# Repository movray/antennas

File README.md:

# Antennas

Printed PCB antennas, designed as code and checked by simulation. One directory per antenna type,
each with its simulation scripts, the KiCad project, etching masks and a `STATUS.md`.
Single-sided boards without parts except the coax: home etching (toner transfer) or any PCB maker.

| Antenna | Type | Band | Simulated on 1.6 mm FR4 | Board |
|---|---|---|---|---|
| [dipole-868](dipole-868/) | Half-wave dipole, reference antenna | LoRa / EU868 | 2.0 dBi, SWR < 1.3 | 147 x 22 mm |
| [moxon-868](moxon-868/) | Moxon rectangle, directional | LoRa / EU868 | 5.3 dBi, F/B 13-14 dB, SWR < 1.2 | 117 x 58 mm |

| dipole-868 | moxon-868 |
|---|---|
|  |  |

> **Status: simulated, not yet measured.** The numbers above come from NEC2 and openEMS simulations.
> The boards have not been built and measured yet; real FR4 (er 4.2-4.7) can move the frequency by
> a few percent. Results of RSSI measurements will be added here.

## How these antennas were made

The antennas were designed together with an LLM: **Claude (Anthropic), working in
[Claude Code](https://claude.com/claude-code)** on the author's machine. The author set the goals
(band, gain, directivity, size, home etching, no VNA available for tuning) and made the decisions;
Claude chose the antenna types together with the author, wrote all scripts in this repository, ran the
simulations and interpreted the results. Nothing was taken from an existing antenna design file.

The workflow, per antenna:

1. **Free-space design with NEC2** (`sim.py`, nec2c, the C port of NEC2): wire model,
   optimises the dimensions for match, gain and front/back ratio in the band.
2. **Check and tuning on FR4 with FDTD** (`sim_fdtd.py`, [openEMS](https://openems.de) with its CSXCAD
   Python interface): NEC2 cannot model the substrate, so the printed strips on 1.6 mm FR4 are simulated
   in 3D, including the dielectric losses. For the Moxon a parameter sweep plus a Nelder-Mead
   optimisation ([SciPy](https://scipy.org)) found the board dimensions.
3. **Circuit as code** (`board.py`, [SKiDL](https://github.com/devbisme/skidl)): antenna and coax feed as
   a netlist.
4. **Readable schematic** (`schematic.py`,
   [kicad-schematic-builder](https://github.com/movray/kicad-schematic-builder)): draws the KiCad schematic
   from the netlist and checks that both agree.
5. **PCB with the KiCad 9 pcbnew Python API** (`layout.py`): writes the antenna footprint from the simulated
   dimensions, places it, adds outline and holes, runs the DRC with `kicad-cli` and writes the etching masks.

Because every step is a script, a change in the simulation flows through to the board by re-running
the scripts; nothing was drawn by hand.

### Lessons learned

* Strips on one side of 1.6 mm FR4 get about **14 % shorter** than in free space (`K_FR4 = 0.86`,
  openEMS, dipole resonant at 868.7 MHz), not the ~5 % that is often assumed.
* Antennas with coupled elements (Moxon, Yagi) **do not just scale** with that factor: the substrate also
  changes the coupling between the elements. The NEC design x 0.86 gave only 7 dB front/back on FR4.
  They have to be tuned in a simulator that models the substrate.
* On FR4 the printed Moxon reaches about 14.5 dB front/back at best (in free space > 25 dB). If you need more,
  build it from wire on a plastic frame; then the NEC2 dimensions apply directly.
* openEMS: simulating only one half of a mirror-symmetric antenna with a PEC wall gives the same result
  (checked against the full model) in about 1/10 of the time.

## Tools to re-run

* nec2c (Debian/Ubuntu package `nec2c`)
* openEMS and CSXCAD with their Python modules (built from source,
  [openEMS-Project](https://github.com/thliebig/openEMS-Project)), plus numpy, scipy, h5py
* KiCad 9 (its Python `pcbnew` module, `kicad-cli`)
* SKiDL and kicad-schematic-builder for the schematic

The `Regenerate` section in each antenna's README lists the commands.

## License

* Hardware (KiCad projects, footprints, etching masks, dimensions, documentation):
  [CERN-OHL-P-2.0](LICENSES/CERN-OHL-P-2.0.txt)
* Scripts (`*.py`): [MIT](LICENSES/MIT.txt)

See [LICENSE](LICENSE). Use, modify, build and sell freely; keep the copyright notice.
No warranty: these are simulated designs, check them before you rely on them.

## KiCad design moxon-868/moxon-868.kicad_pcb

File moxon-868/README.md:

# moxon-868

Directional PCB antenna for LoRa 868 MHz: a Moxon rectangle printed on FR4.
On 1.6 mm FR4 (openEMS): about 5.3 dBi and 13-14 dB front/back ratio in the EU868 band, SWR < 1.2
at 50 Ohm without a matching network. Single-sided, no parts except the coax: home etching or JLCPCB.

Compared to a typical cheap SMA stub antenna (real gain often around 0 dBi) that is about 5 dB more in the
beam direction - roughly 1.8 x the range - and signals from behind are ~25 x weaker.

## Files

| File | Purpose |
|---|---|
| `sim.py` | NEC2 model (nec2c), free-space design for 868 MHz, writes `moxon-868-dims.json` |
| `sim_fdtd.py` | openEMS (FDTD) model on FR4: sweep and optimisation of the board dimensions (`board_mm`) |
| `STATUS.md` | How the FR4 dimensions were found, all simulation results |
| `moxon-868-dims.json` | Simulated dimensions: free space and on FR4 (input for `layout.py`) |
| `board.py` | Circuit (SKiDL): antenna AE1 and coax feed J1 |
| `schematic.py` | Draws the schematic with [kicad-schematic-builder](https://github.com/movray/kicad-schematic-builder) and checks it against the netlist |
| `moxon-868.kicad_sch` | Generated schematic |
| `layout.py` | Writes the antenna and feed footprints from the dimensions, builds the PCB, DRC, etching masks |
| `moxon-868.pretty/` | Generated footprints `Moxon_868` and `CoaxFeed_Gap2mm` |
| `moxon-868.kicad_pcb` | Generated PCB (open in KiCad) |
| `moxon-868-etch-mirrored.pdf` | Etching mask for toner transfer (mirrored, 1:1 on A4) |
| `moxon-868-etch-topview.pdf` | Same mask unmirrored, as seen from the copper side (for checking) |

## Regenerate

```bash
/usr/bin/python3 sim.py          # NEC2 optimisation -> moxon-868-dims.json (needs nec2c on the PATH)
~/.venvs/openems/bin/python sim_fdtd.py --sweep            # FR4: grid search (~30 min, 2 runs x 4 threads)
~/.venvs/openems/bin/python sim_fdtd.py --optimize s,C,r   # FR4: tune, writes board_mm
python board.py                  # circuit -> netlist (runs SKiDL ERC; Python with skidl)
python schematic.py              # netlist -> schematic, fails if the connectivity differs
kicad-cli sch erc moxon-868.kicad_sch
/usr/bin/python3 layout.py       # dims + schematic netlist -> footprints + PCB, DRC, etching masks
```

`~/.venvs/openems` is a Python venv with the openEMS / CSXCAD modules; `/usr/bin/python3` is used where
KiCad's `pcbnew` module is needed. Without root, nec2c can be unpacked from the Debian package
(`apt-get download nec2c && dpkg -x nec2c_*.deb ~/.local/opt/nec2c`) and linked into the PATH.

## Antenna

```
        <---------------- A ---------------->
        +----------------+  +---------------+     driven element, feed gap 2 mm in the middle
        |               J1 (coax pads)      |     tails B
        |                 :                 |
                          :  coax                 gap C
        |                 :                 |     tails D
        +-----------------:-----------------+     reflector
                          :
                      to SMA                       beam -> up (towards the driven element)
```

| Dimension | Free space (NEC) | On FR4 (openEMS) |
|---|---|---|
| A (width, strip centre lines) | 123.3 mm | 98.1 mm |
| B (driven element tails) | 15.5 mm | 12.3 mm |
| C (gap between the tails) | 7.1 mm | 12.2 mm |
| D (reflector tails) | 23.6 mm | 20.6 mm |
| E (depth = B + C + D) | 46.2 mm | 45.1 mm |

Copper strips 3 mm wide, board 117 x 58 mm.

The FR4 dimensions do **not** follow from the free-space ones by one factor: the substrate shortens
the strips by ~14 % and also changes the coupling across the gap C. They were tuned directly in openEMS
(1.6 mm FR4, er 4.4, tan d 0.02): A, B, D x 0.86 x 0.925, the reflector tails D another x 1.094, and C
12.2 mm. See `STATUS.md`.

openEMS on FR4, at 50 Ohm:

| f / MHz | SWR | Gain / dBi | F/B / dB |
|---|---|---|---|
| 850 | 1.67 | 5.4 | 11 |
| 860 | 1.18 | 5.3 | 13 |
| 870 | 1.13 | 5.2 | 14 |
| 880 | 1.35 | 5.1 | 15 |
| 900 | 1.62 | 4.8 | 13 |

On FR4 the front/back ratio peaks at ~14.5 dB (NEC in free space: > 25 dB); this is the best the
printed version reaches. A Moxon from 2 mm copper wire on a plastic frame would reach the NEC values.
If a measurement shows that the antenna works best at another frequency, scale A, B, C, D by
868 / f_best.

Polarisation is in the board plane: for LoRa nodes with vertical whips, mount the board **vertically**
(elements vertical), beam pointing at the counter station.

## Feed

J1 are two solder pads on the feed gap. Use a 50 Ohm pigtail RG316 (or RG174) with an SMA socket at the
other end (e.g. "SMA female bulkhead RG316 15 cm"):

* centre conductor to the **left** pad (pad 1), shield to the **right** pad (pad 2), keep the unshielded
  part as short as possible (< 3 mm)
* the cable runs straight down along the centre line, across the reflector, at right angles to the elements;
  two cable ties through the 2.2 mm hole pairs hold it there
* optional: a clip-on ferrite or a few ferrite beads on the cable right behind the reflector
  (stops currents on the cable shield)

M3 holes left and right: use nylon screws and keep metal away from the tails.

## Etching (toner transfer)

`layout.py` writes the masks after a clean DRC: copper black, board outline as cutting line, the holes
left open as drill marks. Print `moxon-868-etch-mirrored.pdf` on a laser printer at **100 % / actual size**
and check the size: the outline is 117 x 58 mm. For JLCPCB: 1.6 mm FR4, 1 oz, any colour; the solder mask
covers the antenna, only the J1 pads are open.

## Testing without a VNA

Two LoRa modules (e.g. RFM95 / SX1276 / SX1262 on a microcontroller): one sends packets at a fixed spot,
the other logs RSSI and SNR at a distance (> 10 m, outdoors or in a long corridor). Swap only the
antenna on the receiver:

* gain: Moxon pointed at the sender vs. the reference dipole (`../dipole-868`, 2.15 dBi) vs. the bought antenna
* front/back: Moxon pointed at the sender vs. turned by 180 deg - about 10-14 dB expected (multipath indoors
  makes it less)
* average several readings per position; a single RSSI value scatters by a few dB

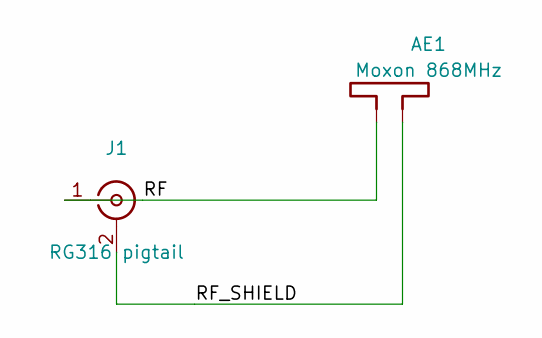
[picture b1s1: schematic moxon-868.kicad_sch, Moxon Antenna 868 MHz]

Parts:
AE1: Moxon 868MHz; Moxon_868
J1: RG316 pigtail; CoaxFeed_Gap2mm

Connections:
/RF: AE1.1, J1.1 (In)
/RF_SHIELD: AE1.2, J1.2 (Ext)

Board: 2 copper layers, 8 parts (0 on the bottom side), 2 nets, no tracks yet.

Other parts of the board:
H1, H2: MountingHole_3.2mm_M3
H3, H4, H5, H6: MountingHole_2.2mm_M2
